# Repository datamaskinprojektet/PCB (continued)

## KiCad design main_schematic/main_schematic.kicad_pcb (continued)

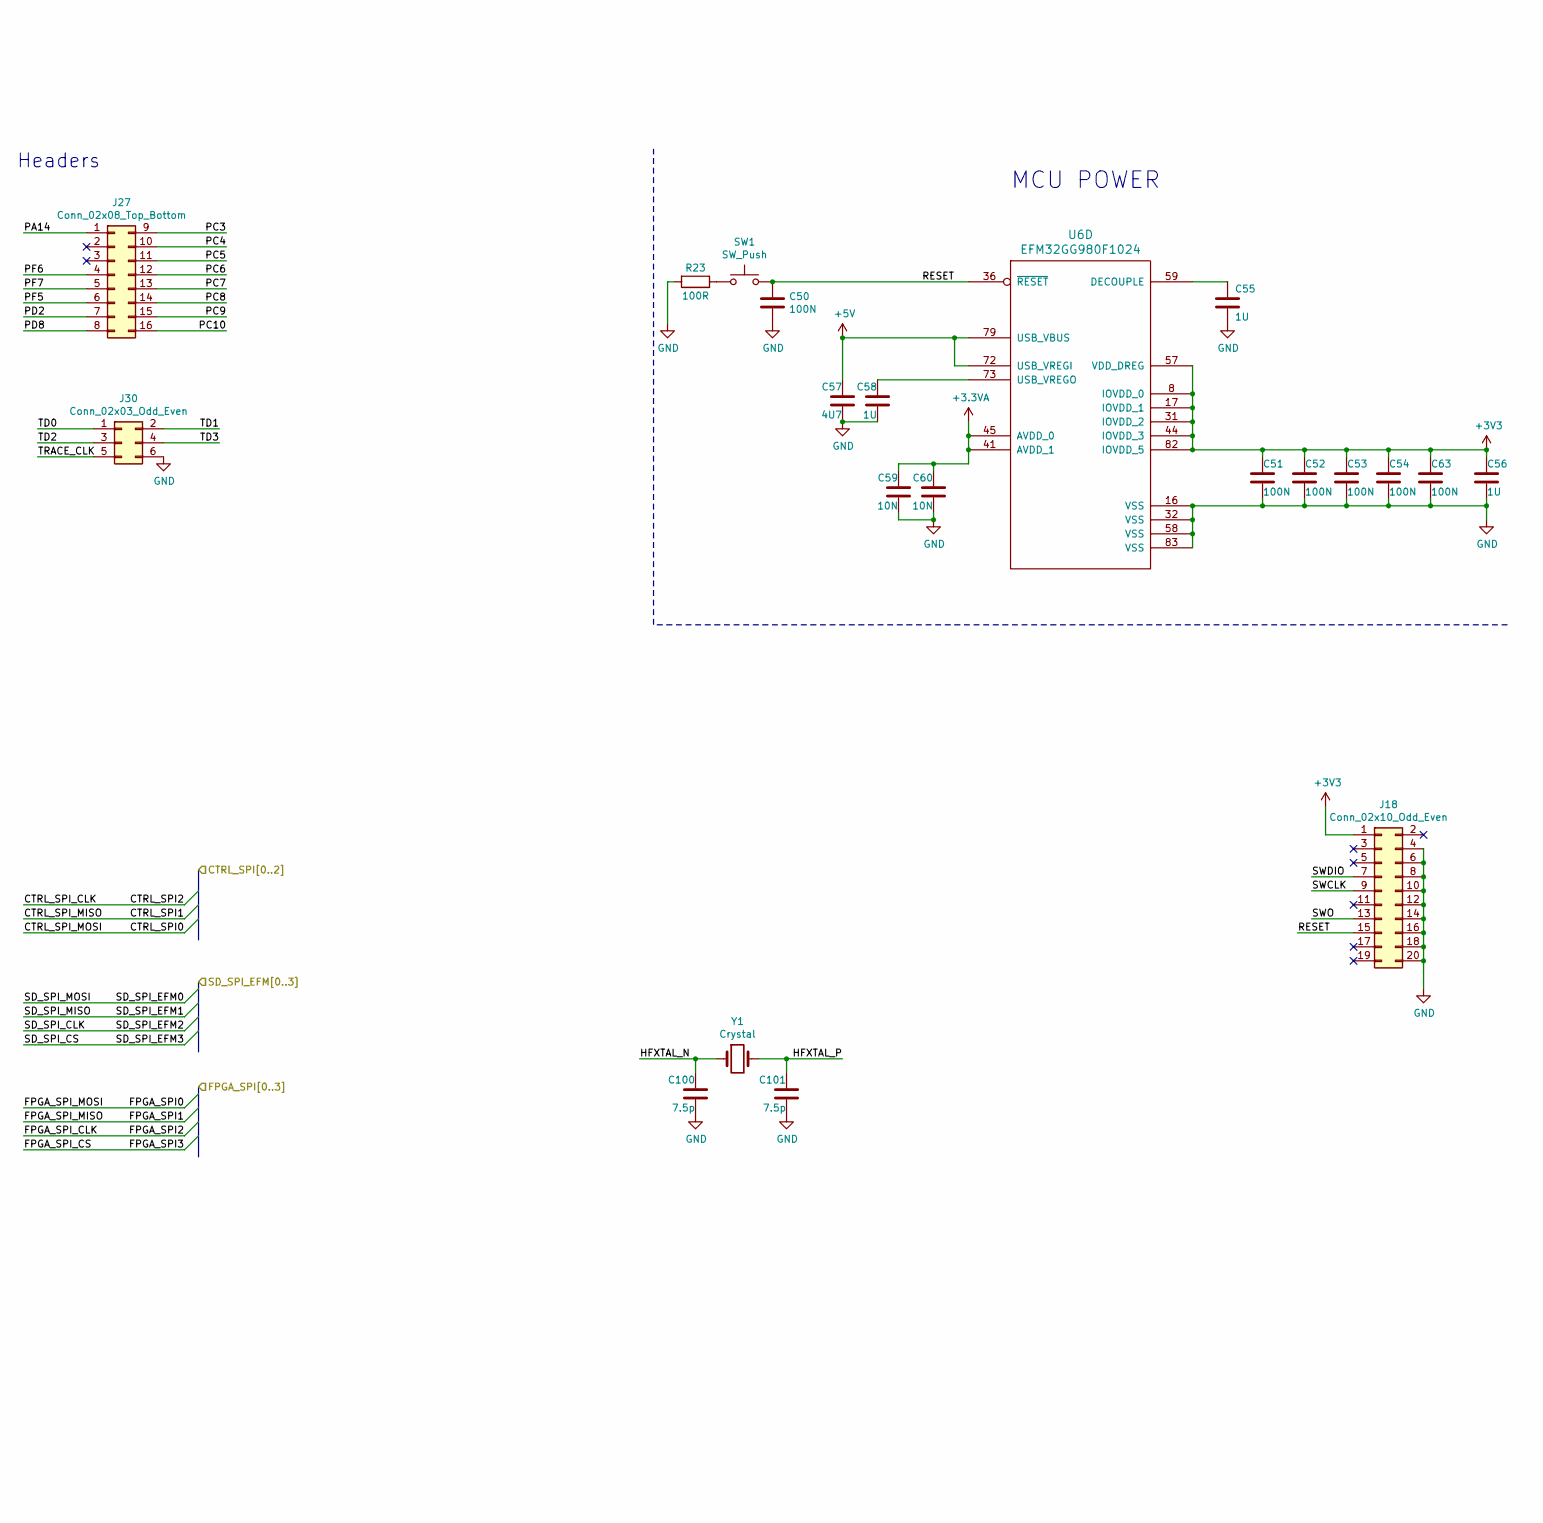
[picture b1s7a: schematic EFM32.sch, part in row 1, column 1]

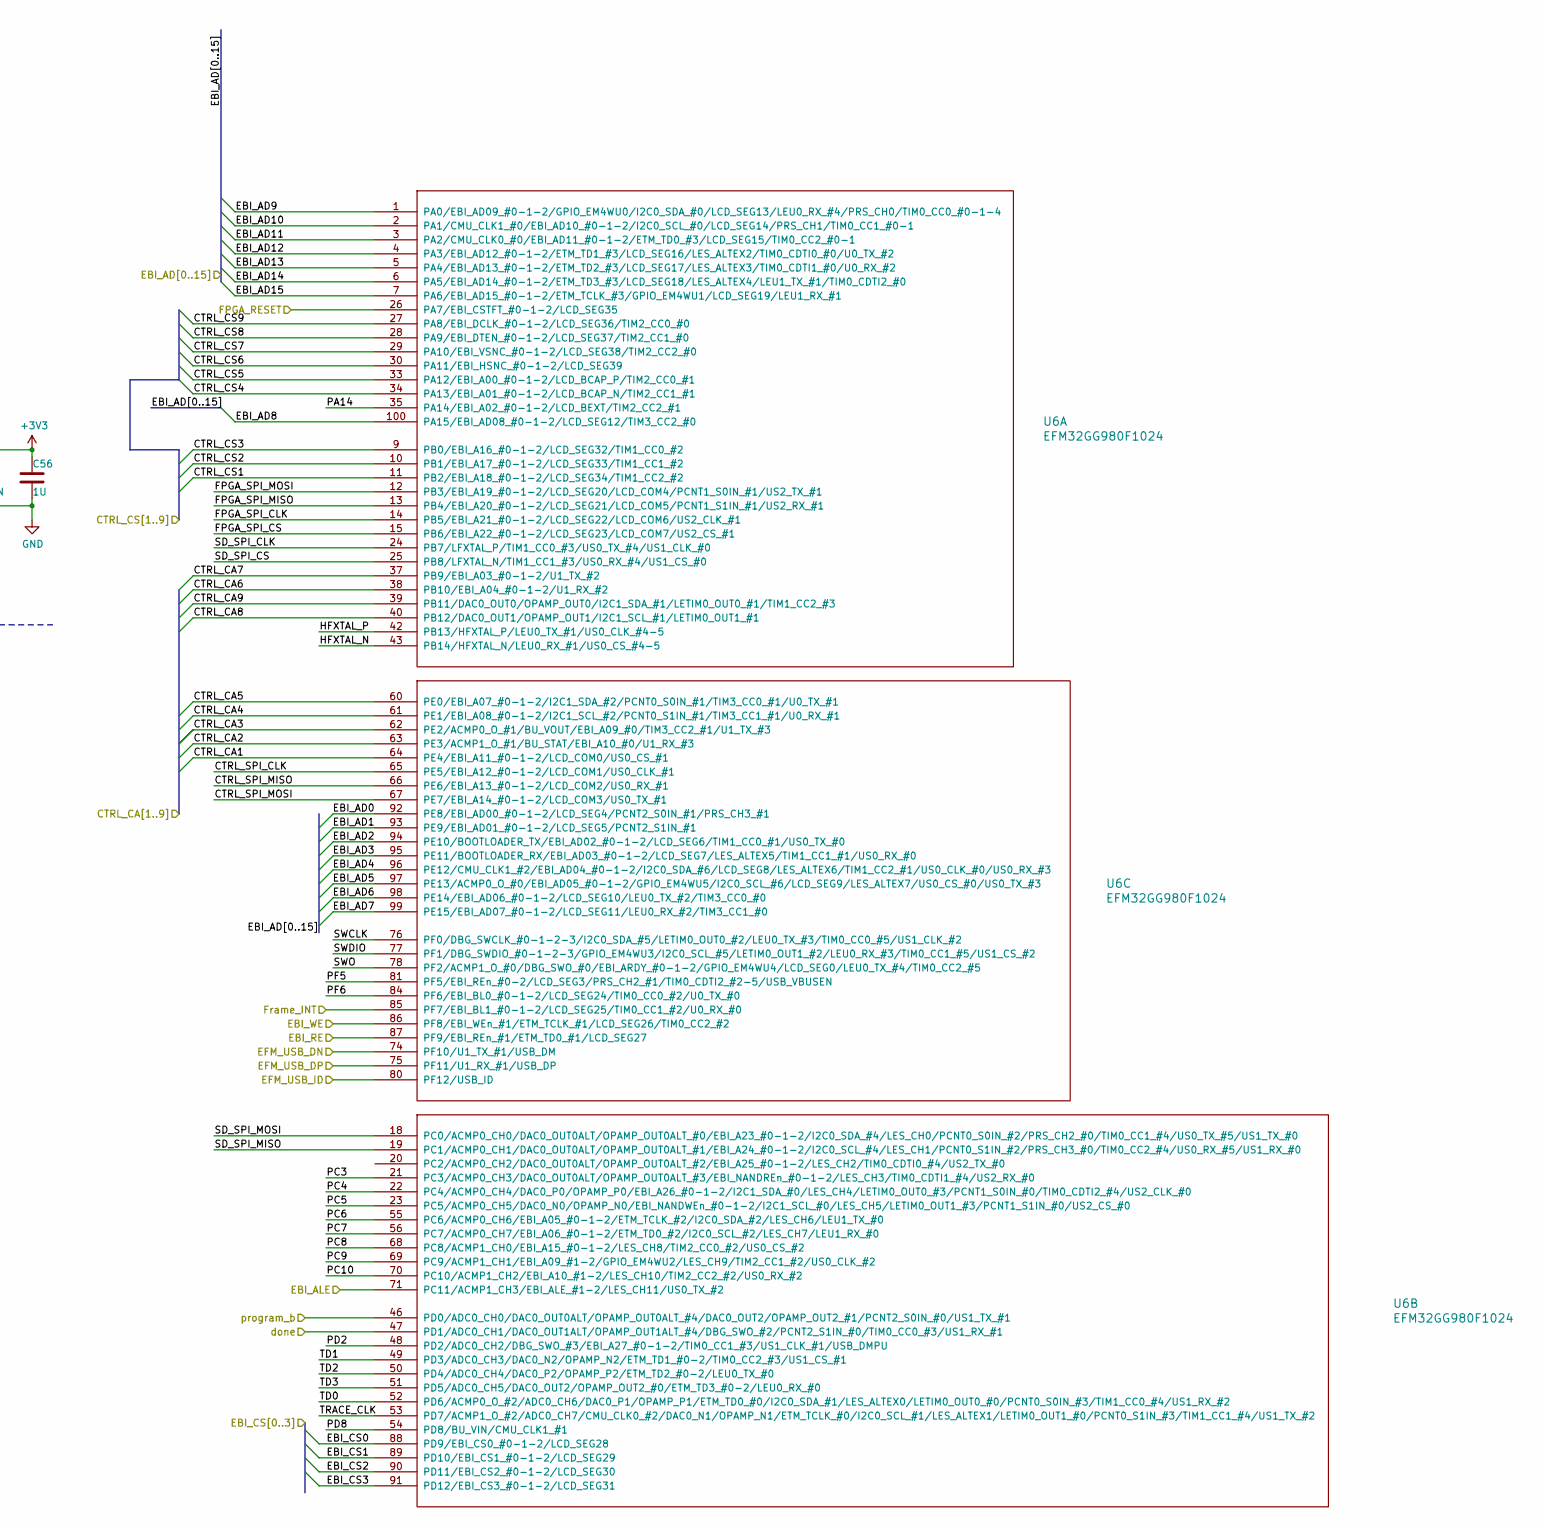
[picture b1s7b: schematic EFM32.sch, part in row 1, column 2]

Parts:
C50, C51, C52, C53, C54, C63: 100N; C_0805_2012Metric
C55, C56, C58: 1U; C_0805_2012Metric
C57: 4U7; C_0805_2012Metric
C59, C60: 10N; C_0805_2012Metric
C100, C101: 7.5p; C_0805_2012Metric
J18: Conn_02x10_Odd_Even; PinHeader_2x10_P2.54mm_Vertical_SMD
J27: Conn_02x08_Top_Bottom; PinHeader_2x08_P2.54mm_Vertical
J30: Conn_02x03_Odd_Even; PinHeader_2x03_P2.54mm_Vertical
R23: 100R; R_0805_2012Metric
SW1: SW_Push; SW_SPST_B3S-1000
U6: EFM32GG980F1024; LQFP-100_14x14mm_P0.5mm
Y1: Crystal; Crystal_SMD_TXC_7A-2Pin_5x3.2mm

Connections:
+3.3VA: C59.1, C60.1, U6.41 (AVDD_1), U6.45 (AVDD_0); also elsewhere on the board
+5V: C57.1, U6.72 (USB_VREGI), U6.79 (USB_VBUS); also elsewhere on the board
/Controller/CTRL_CA1: U6.64 (PE4/EBI_A11_#0-1-2/LCD_COM0/US0_CS_#1); also elsewhere on the board
/Controller/CTRL_CA2: U6.63 (PE3/ACMP1_O_#1/BU_STAT/EBI_A10_#0/U1_RX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); also elsewhere on the board
/Controller/CTRL_CA3: U6.62 (PE2/ACMP0_O_#1/BU_VOUT/EBI_A09_#0/TIM3_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); also elsewhere on the board
/Controller/CTRL_CA4: U6.61 (PE1/EBI_A08_#0-1-2/I2C1_SCL_#2/PCNT0_S1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); also elsewhere on the board
/Controller/CTRL_CS1: U6.11 (PB2/EBI_A18_#0-1-2/LCD_SEG34/TIM1_CC2_#2); also elsewhere on the board
/Controller/CTRL_CS2: U6.10 (PB1/EBI_A17_#0-1-2/LCD_SEG33/TIM1_CC1_#2); also elsewhere on the board
/Controller/CTRL_CS3: U6.9 (PB0/EBI_A16_#0-1-2/LCD_SEG32/TIM1_CC0_#2); also elsewhere on the board
/Controller/CTRL_CS4: U6.34 (PA13/EBI_A01_#0-1-2/LCD_BCAP_N/TIM2_CC1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); also elsewhere on the board
/Controller/CTRL_SPI0: U6.67 (PE7/EBI_A14_#0-1-2/LCD_COM3/US0_TX_#1)
/Controller/CTRL_SPI1: U6.66 (PE6/EBI_A13_#0-1-2/LCD_COM2/US0_RX_#1)
/Controller/CTRL_SPI2: U6.65 (PE5/EBI_A12_#0-1-2/LCD_COM1/US0_CLK_#1)
/EBI_ALE: U6.71 (PC11/ACMP1_CH3/EBI_ALE_#1-2/LES_CH11/US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); also elsewhere on the board
/EBI_RE: U6.87 (PF9/EBI_REn_#1/ETM_TD0_#1/LCD_SEG27); also elsewhere on the board
/EBI_WE: U6.86 (PF8/EBI_WEn_#1/ETM_TCLK_#1/LCD_SEG26/TI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); also elsewhere on the board
/EFM32/CTRL_CA5: U6.60 (PE0/EBI_A07_#0-1-2/I2C1_SDA_#2/PCNT0_S0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)
/EFM32/CTRL_CA6: U6.38 (PB10/EBI_A04_#0-1-2/U1_RX_#2)
/EFM32/CTRL_CA7: U6.37 (PB9/EBI_A03_#0-1-2/U1_TX_#2)
/EFM32/CTRL_CA8: U6.40 (PB12/DAC0_OUT1/OPAMP_OUT1/I2C1_SCL_#1/L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)
/EFM32/CTRL_CA9: U6.39 (PB11/DAC0_OUT0/OPAMP_OUT0/I2C1_SDA_#1/L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)
/EFM32/CTRL_CS5: U6.33 (PA12/EBI_A00_#0-1-2/LCD_BCAP_P/TIM2_CC0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)
/EFM32/CTRL_CS6: U6.30 (PA11/EBI_HSNC_#0-1-2/LCD_SEG39)
/EFM32/CTRL_CS7: U6.29 (PA10/EBI_VSNC_#0-1-2/LCD_SEG38/TIM2_CC2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)
/EFM32/CTRL_CS8: U6.28 (PA9/EBI_DTEN_#0-1-2/LCD_SEG37/TIM2_CC1_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)
/EFM32/CTRL_CS9: U6.27 (PA8/EBI_DCLK_#0-1-2/LCD_SEG36/TIM2_CC0_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)
/EFM32/EBI_AD4: U6.96 (PE12/CMU_CLK1_#2/EBI_AD04_#0-1-2/I2C0_S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); also elsewhere on the board
/EFM32/EBI_AD5: U6.97 (PE13/ACMP0_O_#0/EBI_AD05_#0-1-2/GPIO_EM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); also elsewhere on the board
/EFM32/EBI_AD6: U6.98 (PE14/EBI_AD06_#0-1-2/LCD_SEG10/LEU0_TX_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); also elsewhere on the board
/EFM32/EBI_AD7: U6.99 (PE15/EBI_AD07_#0-1-2/LCD_SEG11/LEU0_RX_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); also elsewhere on the board
/EFM32/EBI_AD8: U6.100 (PA15/EBI_AD08_#0-1-2/LCD_SEG12/TIM3_CC2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); also elsewhere on the board
/EFM32/EBI_AD9: U6.1 (PA0/EBI_AD09_#0-1-2/GPIO_EM4WU0/I2C0_SD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); also elsewhere on the board
/EFM32/EBI_AD10: U6.2 (PA1/CMU_CLK1_#0/EBI_AD10_#0-1-2/I2C0_SC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); also elsewhere on the board
/EFM32/EBI_AD11: U6.3 (PA2/CMU_CLK0_#0/EBI_AD11_#0-1-2/ETM_TD0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); also elsewhere on the board
/EFM32/EBI_AD12: U6.4 (PA3/EBI_AD12_#0-1-2/ETM_TD1_#3/LCD_SEG1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); also elsewhere on the board
/EFM32/EBI_AD13: U6.5 (PA4/EBI_AD13_#0-1-2/ETM_TD2_#3/LCD_SEG1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); also elsewhere on the board
/EFM32/EBI_AD14: U6.6 (PA5/EBI_AD14_#0-1-2/ETM_TD3_#3/LCD_SEG1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); also elsewhere on the board
/EFM32/EBI_AD15: U6.7 (PA6/EBI_AD15_#0-1-2/ETM_TCLK_#3/GPIO_EM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); also elsewhere on the board
/EFM32/EFM_USB_DN: U6.74 (PF10/U1_TX_#1/USB_DM); also elsewhere on the board
/EFM32/EFM_USB_DP: U6.75 (PF11/U1_RX_#1/USB_DP); also elsewhere on the board
/EFM32/EFM_USB_ID: U6.80 (PF12/USB_ID); also elsewhere on the board
/EFM32/FPGA_SPI0: U6.12 (PB3/EBI_A19_#0-1-2/LCD_SEG20/LCD_COM4/P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); also elsewhere on the board
/EFM32/FPGA_SPI1: U6.13 (PB4/EBI_A20_#0-1-2/LCD_SEG21/LCD_COM5/P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); also elsewhere on the board
/EFM32/FPGA_SPI2: U6.14 (PB5/EBI_A21_#0-1-2/LCD_SEG22/LCD_COM6/U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); also elsewhere on the board
/EFM32/FPGA_SPI3: U6.15 (PB6/EBI_A22_#0-1-2/LCD_SEG23/LCD_COM7/U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); also elsewhere on the board
/EFM32/HFXTAL_N: C100.1, U6.43 (PB14/HFXTAL_N/LEU0_RX_#1/US0_CS_#4-5), Y1.1
/EFM32/HFXTAL_P: C101.1, U6.42 (PB13/HFXTAL_P/LEU0_TX_#1/US0_CLK_#4-5), Y1.2
/EFM32/PA14: J27.1, U6.35 (PA14/EBI_A02_#0-1-2/LCD_BEXT/TIM2_CC2_#1)
/EFM32/PC3: J27.9, U6.21 (PC3/ACMP0_CH3/DAC0_OUT0ALT/OPAMP_OUT0AL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)
/EFM32/PC4: J27.10, U6.22 (PC4/ACMP0_CH4/DAC0_P0/OPAMP_P0/EBI_A26_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)
/EFM32/PC5: J27.11, U6.23 (PC5/ACMP0_CH5/DAC0_N0/OPAMP_N0/EBI_NAND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)
/EFM32/PC6: J27.12, U6.55 (PC6/ACMP0_CH6/EBI_A05_#0-1-2/ETM_TCLK_#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)
/EFM32/PC7: J27.13, U6.56 (PC7/ACMP0_CH7/EBI_A06_#0-1-2/ETM_TD0_#2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)
/EFM32/PC8: J27.14, U6.68 (PC8/ACMP1_CH0/EBI_A15_#0-1-2/LES_CH8/TI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)
/EFM32/PC9: J27.15, U6.69 (PC9/ACMP1_CH1/EBI_A09_#1-2/GPIO_EM4WU2/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)
/EFM32/PC10: J27.16, U6.70 (PC10/ACMP1_CH2/EBI_A10_#1-2/LES_CH10/TI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)
/EFM32/PD2: J27.7, U6.48 (PD2/ADC0_CH2/DBG_SWO_#3/EBI_A27_#0-1-2/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)
/EFM32/PD8: J27.8, U6.54 (PD8/BU_VIN/CMU_CLK1_#1)
/EFM32/PF5: J27.6, U6.81 (PF5/EBI_REn_#0-2/LCD_SEG3/PRS_CH2_#1/TI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)
/EFM32/PF6: J27.4, U6.84 (PF6/EBI_BL0_#0-1-2/LCD_SEG24/TIM0_CC0_#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)
/EFM32/PF7: J27.5
/EFM32/RESET: C50.1, J18.15, SW1.2, U6.36 (~RESET~)
/EFM32/SD_SPI_CLK: U6.24 (PB7/LFXTAL_P/TIM1_CC0_#3/US0_TX_#4/US1_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); also elsewhere on the board
/EFM32/SD_SPI_CS: U6.25 (PB8/LFXTAL_N/TIM1_CC1_#3/US0_RX_#4/US1_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); also elsewhere on the board
/EFM32/SD_SPI_EFM0: U6.18 (PC0/ACMP0_CH0/DAC0_OUT0ALT/OPAMP_OUT0AL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); also elsewhere on the board
/EFM32/SD_SPI_EFM1: U6.19 (PC1/ACMP0_CH1/DAC0_OUT0ALT/OPAMP_OUT0AL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); also elsewhere on the board
/EFM32/SWCLK: J18.9, U6.76 (PF0/DBG_SWCLK_#0-1-2-3/I2C0_SDA_#5/LETI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)
/EFM32/SWDIO: J18.7, U6.77 (PF1/DBG_SWDIO_#0-1-2-3/GPIO_EM4WU3/I2C0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)
/EFM32/SWO: J18.13, U6.78 (PF2/ACMP1_O_#0/DBG_SWO_#0/EBI_ARDY_#0-1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)
/EFM32/TD0: J30.1, U6.52 (PD6/ACMP0_O_#2/ADC0_CH6/DAC0_P1/OPAMP_P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)
/EFM32/TD1: J30.2, U6.49 (PD3/ADC0_CH3/DAC0_N2/OPAMP_N2/ETM_TD1_#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)
/EFM32/TD2: J30.3, U6.50 (PD4/ADC0_CH4/DAC0_P2/OPAMP_P2/ETM_TD2_#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)
/EFM32/TD3: J30.4, U6.51 (PD5/ADC0_CH5/DAC0_OUT2/OPAMP_OUT2_#0/ET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)
/EFM32/TRACE_CLK: J30.5, U6.53 (PD7/ACMP1_O_#2/ADC0_CH7/CMU_CLK0_#2/DAC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)
/FPGA_RESET: U6.26 (PA7/EBI_CSTFT_#0-1-2/LCD_SEG35); also elsewhere on the board
/Frame_INT: U6.85 (PF7/EBI_BL1_#0-1-2/LCD_SEG25/TIM0_CC1_#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); also elsewhere on the board
/done: U6.47 (PD1/ADC0_CH1/DAC0_OUT1ALT/OPAMP_OUT1ALT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); also elsewhere on the board
/program_b: U6.46 (PD0/ADC0_CH0/DAC0_OUT0ALT/OPAMP_OUT0ALT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); also elsewhere on the board
GND: C50.2, C51.2, C52.2, C53.2, C54.2, C55.2, C56.2, C57.2, C58.2, C59.2, C60.2, C63.2, C100.2, C101.2, J18.4, J18.6, J18.8, J18.10, J18.12, J18.14, J18.16, J18.18, J18.20, J30.6, R23.2, U6.16 (VSS), U6.32 (VSS), U6.58 (VSS), U6.83 (VSS); also elsewhere on the board
unnamed: C55.1, U6.59 (DECOUPLE)
unnamed: C58.1, U6.73 (USB_VREGO)
unnamed: R23.1, SW1.1

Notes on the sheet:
MCU POWER
Headers

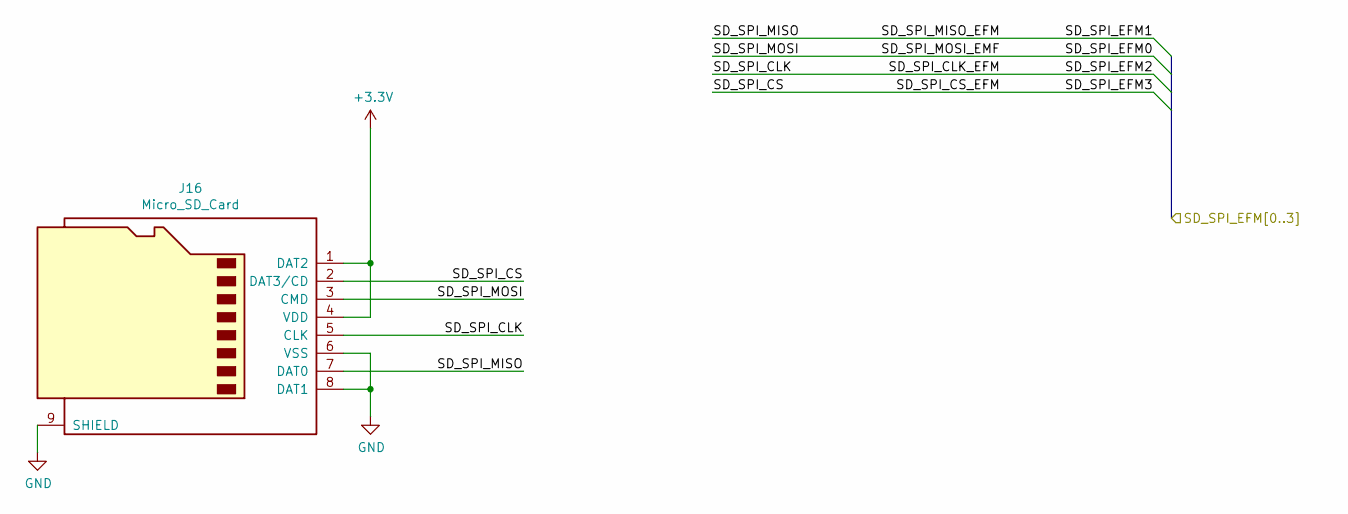
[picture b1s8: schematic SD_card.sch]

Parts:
J16: Micro_SD_Card; mem2051

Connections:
/EFM32/SD_SPI_CLK: J16.5 (CLK); also elsewhere on the board
/EFM32/SD_SPI_CS: J16.2 (DAT3/CD); also elsewhere on the board
/EFM32/SD_SPI_EFM0: J16.3 (CMD); also elsewhere on the board
/EFM32/SD_SPI_EFM1: J16.7 (DAT0); also elsewhere on the board
GND: J16.6 (VSS), J16.8 (DAT1), J16.9 (SHIELD); also elsewhere on the board

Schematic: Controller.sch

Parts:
J1: 2041376-2; 20413762; Mouser Part Number 571-2041376-2

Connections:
/Controller/CTRL_CA1: J1.A7; also elsewhere on the board
/Controller/CTRL_CA2: J1.B7; also elsewhere on the board
/Controller/CTRL_CA3: J1.C7; also elsewhere on the board
/Controller/CTRL_CA4: J1.D7; also elsewhere on the board
/Controller/CTRL_CS1: J1.A6; also elsewhere on the board
/Controller/CTRL_CS2: J1.B6; also elsewhere on the board
/Controller/CTRL_CS3: J1.C6; also elsewhere on the board
/Controller/CTRL_CS4: J1.D6; also elsewhere on the board
/Controller/CTRL_MISO: J1.A3, J1.B3, J1.C3, J1.D3
/Controller/CTRL_MOSI: J1.A4, J1.B4, J1.C4, J1.D4
/Controller/CTRL_SCK: J1.A5, J1.B5, J1.C5, J1.D5
GND: J1.A8, J1.B8, J1.C8, J1.D8; also elsewhere on the board

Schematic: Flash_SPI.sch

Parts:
C49: 100n; C_0805_2012Metric
R17: 2.4k; R_0805_2012Metric
R19, R21: 4.7k; R_0805_2012Metric
U5: S25FL127FL; SOIC-8_5.275x5.275mm_P1.27mm

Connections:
/FPGA/Flash_CLK: U5.6 (CLK); also elsewhere on the board
/FPGA/Flash_CS: R17.2, U5.1 (CS#); also elsewhere on the board
/FPGA/Flash_MISO: U5.2 (MISO); also elsewhere on the board
/FPGA/Flash_MOSI: U5.5 (MOSI); also elsewhere on the board
/FPGA/Flash_RESET: R21.2, U5.7 (HOLD#/RESET#); also elsewhere on the board
/FPGA/Flash_WP: R19.2, U5.3 (WP#); also elsewhere on the board
GND: C49.2, U5.4 (GND); also elsewhere on the board

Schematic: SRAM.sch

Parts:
C64: 100n; C_0805_2012Metric
U4: AS6C6416-55TIN; TSOP-I-48_18.4x12mm_P0.5mm

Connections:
unnamed: C64.1, U4.37 (Vcc)
unnamed: C64.2, U4.27 (GND), U4.46 (GND)

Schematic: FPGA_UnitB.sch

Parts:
U3: XC7A100T-FTG256; Xilinx_FTG256

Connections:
/FPGA/FPGA_UnitB/CLK_100MHZ: U3.D4 (IO_L12P_T1_MRCC_35); also elsewhere on the board
/FPGA/FPGA_UnitB/DQ0: U3.R1 (IO_L7N_T1_34)
/FPGA/FPGA_UnitB/DQ1: U3.P1 (IO_L4N_T0_34)
/FPGA/FPGA_UnitB/DQ2: U3.N1 (IO_L4P_T0_34)
/FPGA/FPGA_UnitB/DQ3: U3.R3 (IO_L8P_T1_34)
/FPGA/FPGA_UnitB/DQ4: U3.T4 (IO_L9P_T1_DQS_34)
/FPGA/FPGA_UnitB/DQ8: U3.R2 (IO_L7P_T1_34)
/FPGA/FPGA_UnitB/DQ9: U3.P3 (IO_L5N_T0_34)
/FPGA/FPGA_UnitB/DQ10: U3.T2 (IO_L8N_T1_34)
/FPGA/FPGA_UnitB/DQ11: U3.T3 (IO_L9N_T1_DQS_34)
/FPGA/HDMI_CEC: U3.C6 (IO_L5N_T0_AD13N_35); also elsewhere on the board
/FPGA/HDMI_HPD: U3.C7 (IO_L5P_T0_AD13P_35); also elsewhere on the board
/FPGA/HDMI_SCL: U3.G5 (IO_L16P_T2_35); also elsewhere on the board
/FPGA/HDMI_SDA: U3.G4 (IO_L16N_T2_35); also elsewhere on the board
/FPGA/VGA_HS: U3.D3 (IO_L11N_T1_SRCC_35); also elsewhere on the board
/FPGA/VGA_VS: U3.E3 (IO_L11P_T1_SRCC_35); also elsewhere on the board
/HDMI/HDMI_CK_N: U3.A2 (IO_L8N_T1_AD14N_35); also elsewhere on the board
/HDMI/HDMI_CK_P: U3.B2 (IO_L8P_T1_AD14P_35); also elsewhere on the board
/HDMI/HDMI_D0_N: U3.B1 (IO_L9N_T1_DQS_AD7N_35); also elsewhere on the board
/HDMI/HDMI_D0_P: U3.C1 (IO_L9P_T1_DQS_AD7P_35); also elsewhere on the board
/HDMI/HDMI_D1_N: U3.A4 (IO_L3N_T0_DQS_AD5N_35); also elsewhere on the board
/HDMI/HDMI_D1_P: U3.A5 (IO_L3P_T0_DQS_AD5P_35); also elsewhere on the board
/HDMI/HDMI_D2_N: U3.B5 (IO_L2N_T0_AD12N_35); also elsewhere on the board
/HDMI/HDMI_D2_P: U3.B6 (IO_L2P_T0_AD12P_35); also elsewhere on the board
/VGA/VGA_B1: U3.A3 (IO_L4N_T0_35); also elsewhere on the board
/VGA/VGA_B2: U3.C2 (IO_L7N_T1_AD6N_35); also elsewhere on the board
/VGA/VGA_B3: U3.E2 (IO_L10P_T1_AD15P_35); also elsewhere on the board
/VGA/VGA_B4: U3.F4 (IO_L14P_T2_SRCC_35); also elsewhere on the board
/VGA/VGA_B5: U3.H5 (IO_L18P_T2_35); also elsewhere on the board
/VGA/VGA_G0: U3.F3 (IO_L14N_T2_SRCC_35); also elsewhere on the board
/VGA/VGA_G1: U3.B4 (IO_L4P_T0_35); also elsewhere on the board
/VGA/VGA_G2: U3.F5 (IO_L13P_T2_MRCC_35); also elsewhere on the board
/VGA/VGA_G3: U3.D1 (IO_L10N_T1_AD15N_35); also elsewhere on the board
/VGA/VGA_G4: U3.G1 (IO_L17N_T2_35); also elsewhere on the board
/VGA/VGA_G5: U3.E1 (IO_L15N_T2_DQS_35); also elsewhere on the board
/VGA/VGA_R1: U3.C3 (IO_L7P_T1_AD6P_35); also elsewhere on the board
/VGA/VGA_R2: U3.E5 (IO_L13N_T2_MRCC_35); also elsewhere on the board
/VGA/VGA_R3: U3.G2 (IO_L17P_T2_35); also elsewhere on the board
/VGA/VGA_R4: U3.H4 (IO_L18N_T2_35); also elsewhere on the board
/VGA/VGA_R5: U3.F2 (IO_L15P_T2_DQS_35); also elsewhere on the board
FPGA_GPIO_B9: U3.L5 (IO_0_34); also elsewhere on the board
FPGA_GPIO_B10: U3.L4 (IO_L1P_T0_34); also elsewhere on the board
FPGA_GPIO_B11: U3.M4 (IO_L1N_T0_34); also elsewhere on the board
FPGA_GPIO_B12: U3.M2 (IO_L2P_T0_34); also elsewhere on the board
FPGA_GPIO_B13: U3.M1 (IO_L2N_T0_34); also elsewhere on the board
FPGA_GPIO_B14: U3.N3 (IO_L3P_T0_DQS_34); also elsewhere on the board
FPGA_GPIO_B15: U3.N2 (IO_L3N_T0_DQS_34); also elsewhere on the board
FPGA_GPIO_C0: U3.P4 (IO_L5P_T0_34); also elsewhere on the board
FPGA_GPIO_C1: U3.M5 (IO_L6P_T0_34); also elsewhere on the board
FPGA_GPIO_C2: U3.N4 (IO_L6N_T0_VREF_34); also elsewhere on the board
FPGA_GPIO_C3: U3.P5 (IO_L10P_T1_34); also elsewhere on the board
FPGA_GPIO_C4: U3.E6 (IO_0_35); also elsewhere on the board
FPGA_GPIO_C7: U3.D6 (IO_L6P_T0_35); also elsewhere on the board
FPGA_GPIO_C8: U3.D5 (IO_L6N_T0_VREF_35); also elsewhere on the board
FPGA_GPIO_C9: U3.C4 (IO_L12N_T1_MRCC_35); also elsewhere on the board
FPGA_GPIO_C10: U3.J5 (IO_L19P_T3_35)
FPGA_GPIO_C11: U3.J4 (IO_L19N_T3_VREF_35)
FPGA_GPIO_C12: U3.H2 (IO_L20P_T3_35); also elsewhere on the board
FPGA_GPIO_C13: U3.H1 (IO_L20N_T3_35)
FPGA_GPIO_C14: U3.J3 (IO_L21P_T3_DQS_35); also elsewhere on the board
FPGA_GPIO_C15: U3.H3 (IO_L21N_T3_DQS_35); also elsewhere on the board
FPGA_GPIO_D0: U3.K1 (IO_L22P_T3_35)
FPGA_GPIO_D1: U3.J1 (IO_L22N_T3_35)
FPGA_GPIO_D2: U3.L3 (IO_L23P_T3_35); also elsewhere on the board
FPGA_GPIO_D3: U3.L2 (IO_L23N_T3_35); also elsewhere on the board
FPGA_GPIO_D4: U3.K3 (IO_L24P_T3_35); also elsewhere on the board
FPGA_GPIO_D5: U3.K2 (IO_L24N_T3_35)
FPGA_GPIO_D6: U3.K5 (IO_25_35)

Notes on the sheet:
HEADERS
DEBUG LEDS

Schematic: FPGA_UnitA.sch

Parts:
J2: PMOD1; SMH10602LD
J3: PMOD2; SMH10602LD
J7: PMOD3; SMH10602LD
J8: PMOD4; SMH10602LD
J9: PMOD5; SMH10602LD
J10: PMOD6; SMH10602LD
SW5: RESET_SW_FPGA; SW_SPST_B3S-1000
U3: XC7A100T-FTG256; Xilinx_FTG256

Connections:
/EBI_ALE: U3.D9 (IO_L6N_T0_VREF_15); also elsewhere on the board
/EBI_RE: U3.A9 (IO_L2N_T0_AD8N_15); also elsewhere on the board
/EBI_WE: U3.C9 (IO_L1N_T0_AD0N_15); also elsewhere on the board
/EFM32/EBI_AD4: U3.B12 (IO_L5P_T0_AD9P_15); also elsewhere on the board
/EFM32/EBI_AD5: U3.A13 (IO_L7P_T1_AD2P_15); also elsewhere on the board
/EFM32/EBI_AD6: U3.D15 (IO_L15N_T2_DQS_ADV_B_15); also elsewhere on the board
/EFM32/EBI_AD7: U3.A14 (IO_L7N_T1_AD2N_15); also elsewhere on the board
/EFM32/EBI_AD8: U3.A15 (IO_L9N_T1_DQS_AD3N_15); also elsewhere on the board
/EFM32/EBI_AD9: U3.B14 (IO_L8N_T1_AD10N_15); also elsewhere on the board
/EFM32/EBI_AD10: U3.B15 (IO_L9P_T1_DQS_AD3P_15); also elsewhere on the board
/EFM32/EBI_AD11: U3.B16 (IO_L10N_T1_AD11N_15); also elsewhere on the board
/EFM32/EBI_AD12: U3.C14 (IO_L8P_T1_AD10P_15); also elsewhere on the board
/EFM32/EBI_AD13: U3.D14 (IO_L15P_T2_DQS_15); also elsewhere on the board
/EFM32/EBI_AD14: U3.C16 (IO_L10P_T1_AD11P_15); also elsewhere on the board
/EFM32/EBI_AD15: U3.D16 (IO_L17N_T2_A25_15); also elsewhere on the board
/EFM32/FPGA_SPI0: U3.E13 (IO_L13N_T2_MRCC_15); also elsewhere on the board
/EFM32/FPGA_SPI1: U3.C12 (IO_L11N_T1_SRCC_15); also elsewhere on the board
/EFM32/FPGA_SPI2: U3.D13 (IO_L12P_T1_MRCC_15); also elsewhere on the board
/EFM32/FPGA_SPI3: U3.C13 (IO_L12N_T1_MRCC_15); also elsewhere on the board
/FPGA/BYTE#: U3.P8 (IO_L20P_T3_A08_D24_14)
/FPGA/CE2: U3.P13 (IO_L11N_T1_SRCC_14)
/FPGA/CE#: U3.N13 (IO_L11P_T1_SRCC_14)
/FPGA/FPGA_UnitA/A0: U3.P10 (IO_L14P_T2_SRCC_14)
/FPGA/FPGA_UnitA/A1: U3.R16 (IO_L9N_T1_DQS_D13_14)
/FPGA/FPGA_UnitA/A2: U3.R15 (IO_L9P_T1_DQS_14)
/FPGA/FPGA_UnitA/A3: U3.P16 (IO_L8N_T1_D12_14)
/FPGA/FPGA_UnitA/A4: U3.P15 (IO_L8P_T1_D11_14)
/FPGA/FPGA_UnitA/A5: U3.N16 (IO_L7N_T1_D10_14)
/FPGA/FPGA_UnitA/A6: U3.N14 (IO_L12P_T1_MRCC_14)
/FPGA/FPGA_UnitA/A7: U3.M16 (IO_L7P_T1_D09_14)
/FPGA/FPGA_UnitA/A8: U3.T13 (IO_L16N_T2_A15_D31_14)
/FPGA/FPGA_UnitA/A9: U3.R12 (IO_L15P_T2_DQS_RDWR_B_14)
/FPGA/FPGA_UnitA/A10: U3.T12 (IO_L15N_T2_DQS_DOUT_CSO_B_14)
/FPGA/FPGA_UnitA/A11: U3.P11 (IO_L14N_T2_SRCC_14)
/FPGA/FPGA_UnitA/A12: U3.R11 (IO_L17N_T2_A13_D29_14)
/FPGA/FPGA_UnitA/A13: U3.T10 (IO_L22N_T3_A04_D20_14)
/FPGA/FPGA_UnitA/A14: U3.R10 (IO_L17P_T2_A14_D30_14)
/FPGA/FPGA_UnitA/A15: U3.T9 (IO_L22P_T3_A05_D21_14)
/FPGA/FPGA_UnitA/A16: U3.P9 (IO_L18N_T2_A11_D27_14)
/FPGA/FPGA_UnitA/A17: U3.M15 (IO_L3N_T0_DQS_EMCCLK_14)
/FPGA/FPGA_UnitA/A18: U3.T15 (IO_L10N_T1_D15_14)
/FPGA/FPGA_UnitA/A19: U3.R13 (IO_L16P_T2_CSI_B_14)
/FPGA/FPGA_UnitA/A20: U3.T14 (IO_L10P_T1_D14_14)
/FPGA/FPGA_UnitA/A21: U3.P14 (IO_L12N_T1_MRCC_14)
/FPGA/FPGA_UnitA/DQ5: U3.T5 (IO_L23N_T3_A02_D18_14)
/FPGA/FPGA_UnitA/DQ6: U3.R7 (IO_L24N_T3_A00_D16_14)
/FPGA/FPGA_UnitA/DQ7: U3.R8 (IO_L20N_T3_A07_D23_14)
/FPGA/FPGA_UnitA/DQ12: U3.R5 (IO_L23P_T3_A03_D19_14)
/FPGA/FPGA_UnitA/DQ13: U3.R6 (IO_L24P_T3_A01_D17_14)
/FPGA/FPGA_UnitA/DQ14: U3.T7 (IO_L21P_T3_DQS_14)
/FPGA/FPGA_UnitA/DQ15: U3.T8 (IO_L21N_T3_DQS_A06_D22_14)
/FPGA/FPGA_UnitA/SD_SPI_AUDIO0: U3.N11 (IO_L13P_T2_MRCC_14)
/FPGA/FPGA_UnitA/SD_SPI_AUDIO1: U3.L14 (IO_L4P_T0_D04_14)
/FPGA/FPGA_UnitA/SD_SPI_AUDIO2: U3.M14 (IO_L4N_T0_D05_14)
/FPGA/FPGA_UnitA/SD_SPI_AUDIO3: U3.K13 (IO_L5P_T0_D06_14)
/FPGA/FPGA_UnitA/SD_SPI_AUDIO4: U3.K12 (IO_0_14)
/FPGA/Flash_CS: U3.L12 (IO_L6P_T0_FCS_B_14); also elsewhere on the board
/FPGA/Flash_MISO: U3.J14 (IO_L1N_T0_D01_DIN_14); also elsewhere on the board
/FPGA/Flash_MOSI: U3.J13 (IO_L1P_T0_D00_MOSI_14); also elsewhere on the board
/FPGA/Flash_RESET: U3.K16 (IO_L2N_T0_D03_14); also elsewhere on the board
/FPGA/Flash_WP: U3.K15 (IO_L2P_T0_D02_14); also elsewhere on the board
/FPGA/LB#: U3.L13 (IO_L5N_T0_D07_14)
/FPGA/OE#: U3.N6 (IO_L19N_T3_A09_D25_VREF_14)
/FPGA/UB#: U3.N12 (IO_L13N_T2_MRCC_14)
/FPGA/WE#: U3.M6 (IO_L19P_T3_A10_D26_14)
/FPGA_RESET: SW5.1 (A), U3.D10 (IO_0_15); also elsewhere on the board
/Frame_INT: U3.A8 (IO_L2P_T0_AD8P_15); also elsewhere on the board
FPGA_GPIO_A0: J2.10
FPGA_GPIO_A1: J7.12
FPGA_GPIO_A2: J3.8
FPGA_GPIO_A3: J2.11
FPGA_GPIO_A4: J3.5
FPGA_GPIO_A5: J3.9
FPGA_GPIO_A6: J3.7
FPGA_GPIO_A7: J3.12
FPGA_GPIO_A8: J3.10
FPGA_GPIO_A9: J8.5
FPGA_GPIO_A10: J2.12
FPGA_GPIO_A11: J8.8
FPGA_GPIO_A12: J7.6
FPGA_GPIO_A13: J3.11
FPGA_GPIO_A14: J3.6
FPGA_GPIO_A15: J7.9
FPGA_GPIO_B0: J7.7
FPGA_GPIO_B1: J7.10
FPGA_GPIO_B2: J7.11
FPGA_GPIO_B3: J7.5
FPGA_GPIO_B4: J7.8
FPGA_GPIO_B5: J8.9
FPGA_GPIO_B6: J8.6, U3.M12 (IO_L6N_T0_D08_VREF_14)
FPGA_GPIO_B7: J8.7, U3.N9 (IO_L18P_T2_A12_D28_14)
FPGA_GPIO_B8: J9.7, U3.P6 (IO_25_14)
FPGA_GPIO_B9: J10.6; also elsewhere on the board
FPGA_GPIO_B10: J10.7; also elsewhere on the board
FPGA_GPIO_B11: J10.12; also elsewhere on the board
FPGA_GPIO_B12: J10.5; also elsewhere on the board
FPGA_GPIO_B13: J9.5; also elsewhere on the board
FPGA_GPIO_B14: J9.12; also elsewhere on the board
FPGA_GPIO_B15: J9.6; also elsewhere on the board
FPGA_GPIO_C0: J9.11; also elsewhere on the board
FPGA_GPIO_C1: J9.8; also elsewhere on the board
FPGA_GPIO_C2: J9.10; also elsewhere on the board
FPGA_GPIO_C3: J9.9; also elsewhere on the board
FPGA_GPIO_C4: J8.10; also elsewhere on the board
FPGA_GPIO_C5: J2.6
FPGA_GPIO_C6: J2.7
FPGA_GPIO_C7: J2.9; also elsewhere on the board
FPGA_GPIO_C8: J2.5; also elsewhere on the board
FPGA_GPIO_C9: J2.8; also elsewhere on the board
FPGA_GPIO_C12: J8.11; also elsewhere on the board
FPGA_GPIO_C14: J10.10; also elsewhere on the board
FPGA_GPIO_C15: J8.12; also elsewhere on the board
FPGA_GPIO_D2: J10.8; also elsewhere on the board
FPGA_GPIO_D3: J10.9; also elsewhere on the board
FPGA_GPIO_D4: J10.11; also elsewhere on the board
GND: J2.3, J2.4, J3.3, J3.4, J7.3, J7.4, J8.3, J8.4, J9.3, J9.4, J10.3, J10.4, U3.L15 (IO_L3P_T0_DQS_PUDC_B_14); also elsewhere on the board

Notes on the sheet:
HEADERS

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
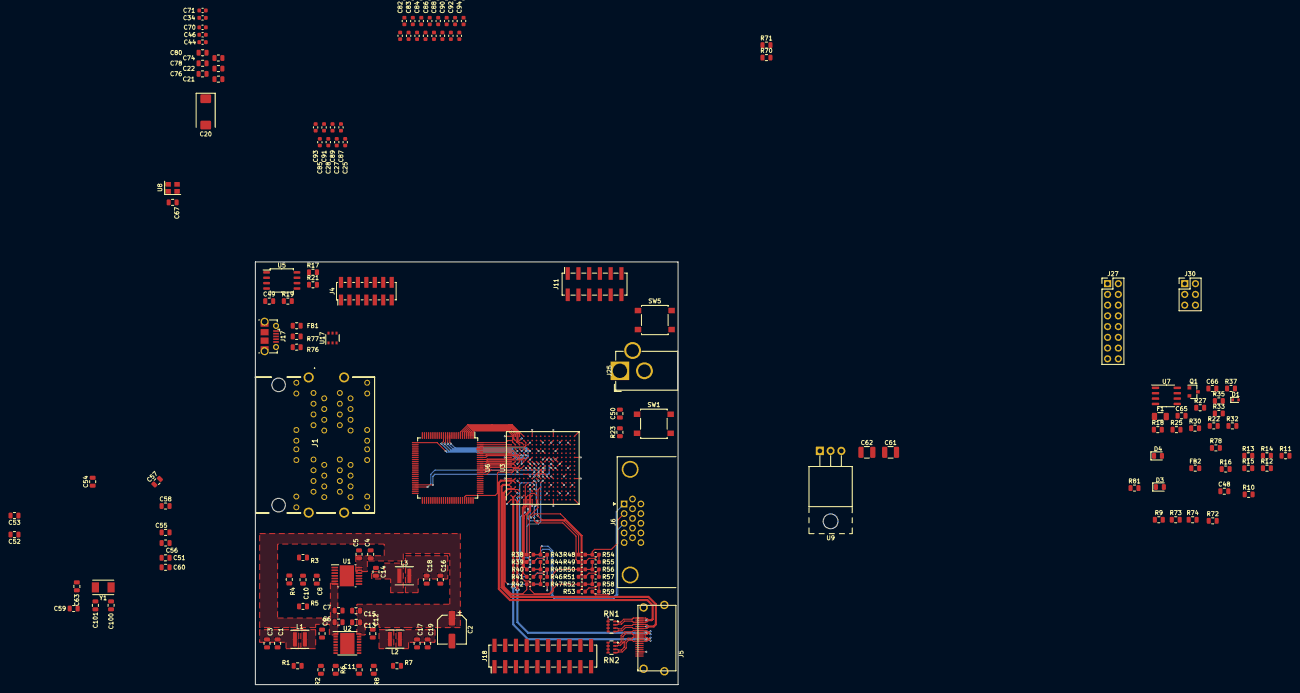
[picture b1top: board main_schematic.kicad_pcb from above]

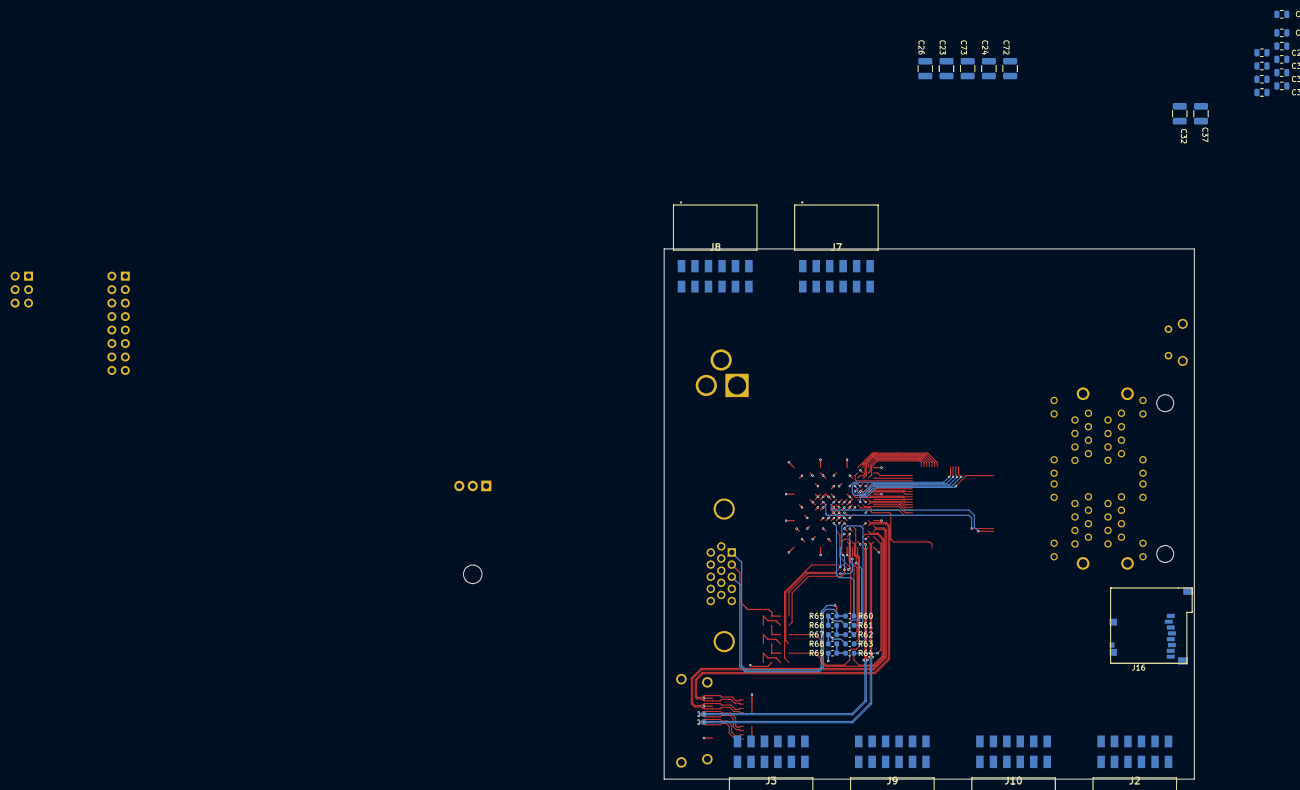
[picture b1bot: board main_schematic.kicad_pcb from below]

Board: 6 copper layers, 100.0 x 100.0 mm, 204 parts (34 on the bottom side), 196 nets.

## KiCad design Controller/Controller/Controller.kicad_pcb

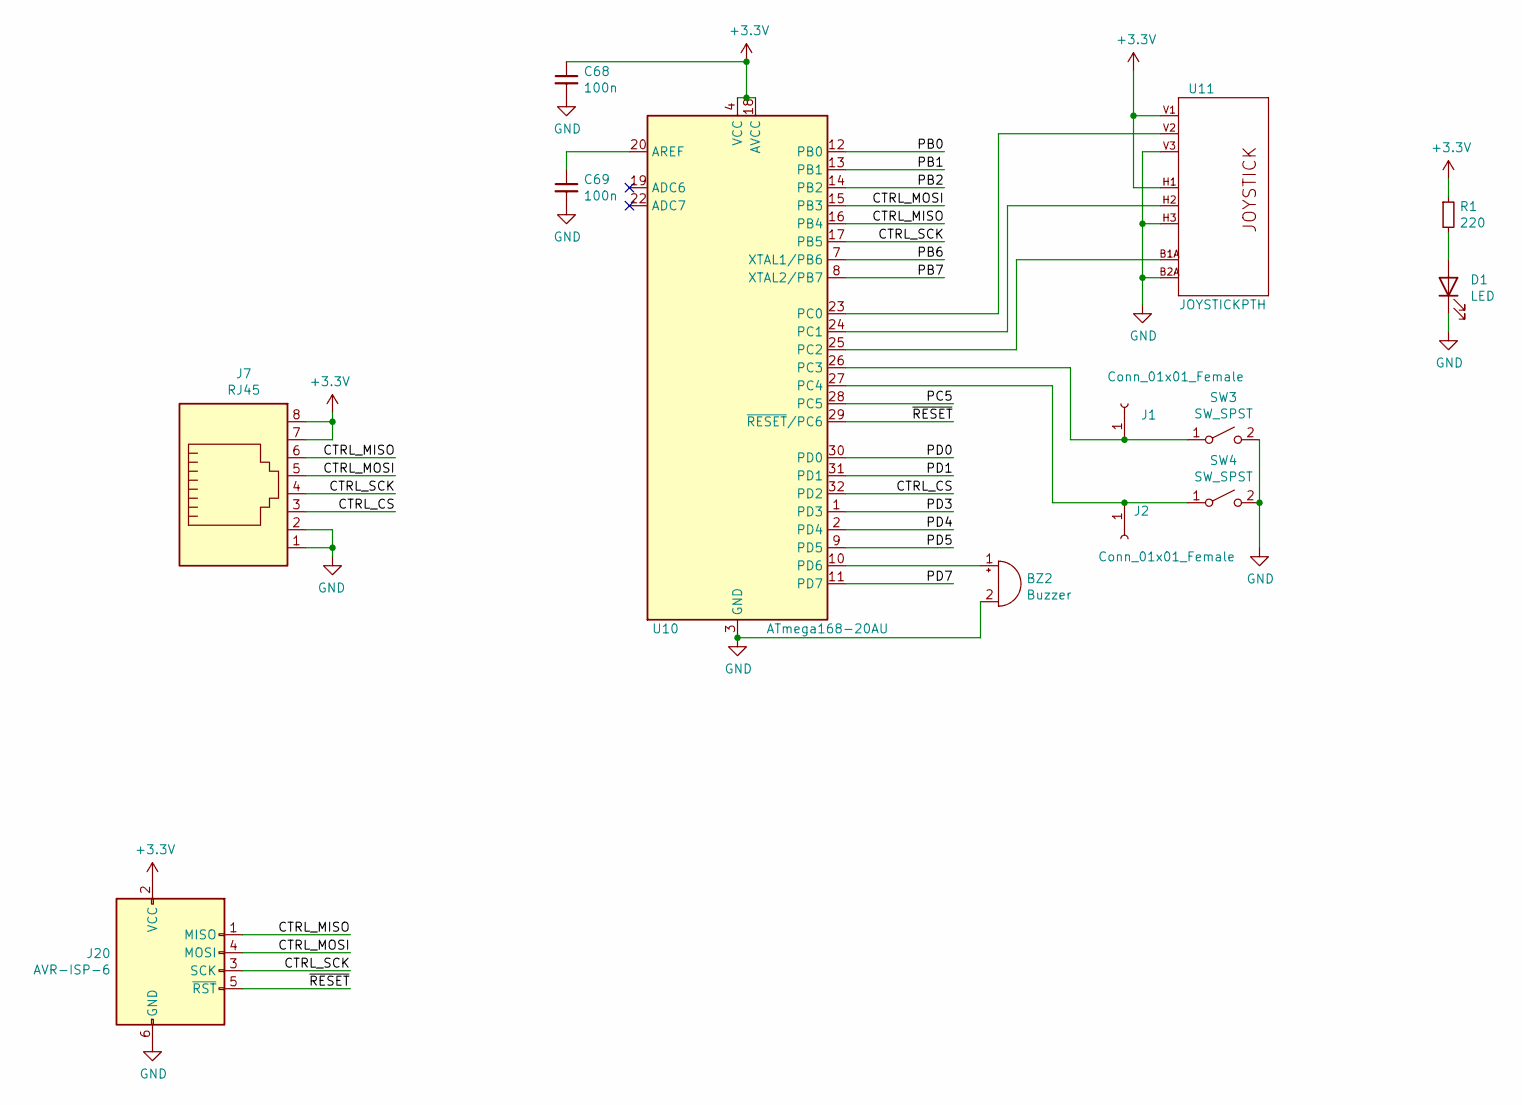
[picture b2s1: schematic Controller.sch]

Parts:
BZ2: Buzzer; Buzzer_12x9.5RM7.6
C68, C69: 100n; C_0805_2012Metric
D1: LED; LED_D5.0mm
J1, J2: Conn_01x01_Female; PinHeader_1x01_P2.54mm_Vertical
J7: RJ45; RJ45_Amphenol_54602-x08_Horizontal
J20: AVR-ISP-6; IDC-Header_2x03_P2.54mm_Vertical
R1: 220; R_0805_2012Metric
SW3, SW4: SW_SPST; SW_SPST_B3S-1000
U10: ATmega168-20AU; TQFP-32_7x7mm_P0.8mm
U11: JOYSTICKPTH; JOYSTICK

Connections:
+3V3: C68.1, J7.7, J7.8, J20.2 (VCC), R1.1, U10.4 (VCC), U10.6 (VCC), U10.18 (AVCC), U11.H1 (H+), U11.V1 (V+)
/CTRL_CS: J7.3, U10.32 (PD2)
/CTRL_MISO: J7.6, J20.1 (MISO), U10.16 (PB4)
/CTRL_MOSI: J7.5, J20.4 (MOSI), U10.15 (PB3)
/CTRL_SCK: J7.4, J20.3 (SCK), U10.17 (PB5)
/PB0: U10.12 (PB0)
/PB1: U10.13 (PB1)
/PB2: U10.14 (PB2)
/PB6: U10.7 (XTAL1/PB6)
/PB7: U10.8 (XTAL2/PB7)
/PC5: U10.28 (PC5)
/PD0: U10.30 (PD0)
/PD1: U10.31 (PD1)
/PD3: U10.1 (PD3)
/PD4: U10.2 (PD4)
/PD5: U10.9 (PD5)
/PD7: U10.11 (PD7)
/~RESET~: J20.5 (~RST), U10.29 (~RESET~/PC6)
GND: BZ2.2 (+), C68.2, C69.2, D1.1 (K), J7.1, J7.2, J20.6 (GND), SW3.2 (B), SW4.2 (B), U10.3 (GND), U10.5 (GND), U10.21 (GND), U11.B2A (SEL-), U11.H3 (H-), U11.V3 (V-)
unnamed: BZ2.1 (-), U10.10 (PD6)
unnamed: C69.1, U10.20 (AREF)
unnamed: D1.2 (A), R1.2
unnamed: J1.1, SW3.1 (A), U10.26 (PC3)
unnamed: J2.1, SW4.1 (A), U10.27 (PC4)
unnamed: U10.23 (PC0), U11.V2 (V)
unnamed: U10.24 (PC1), U11.H2 (H)
unnamed: U10.25 (PC2), U11.B1A (SEL+)
